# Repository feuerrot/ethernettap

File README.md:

# Ethernettap

Passive ethernet tap, build after [this](http://itgeekchronicles.co.uk/2011/09/21/random-diy-passive-ethernet-tap-or-pet/) instruction.

I've never tested the layout, so you maybe want to do that first, because I'm not responsible for whatever you do with this hardware.

The RJ45-connector is from [Pollin](http://www.pollin.de) and it's called [Western-Modularbuchse FCI 748729-3011](http://www.pollin.de/shop/dt/OTk5ODQ1OTk-/Bauelemente_Bauteile/Mechanische_Bauelemente/Steckverbinder_Klemmen/Western_Modularbuchse_FCI_748729_3011.html) and 4 of them costs 1,20€ so maybe the whole tap costs something below 5€.

## Layout

### Top

### Bottom

### Combined

### Combined as gif

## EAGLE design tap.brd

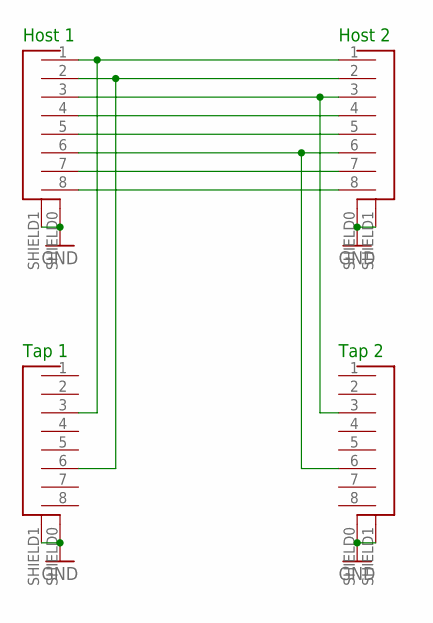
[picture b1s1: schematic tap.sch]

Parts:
HOST1, HOST2: 451000; RJ45
TAP1, TAP2: 451000; RJ45

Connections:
GND: HOST1.SHIELD0, HOST1.SHIELD1, HOST2.SHIELD0, HOST2.SHIELD1, TAP1.SHIELD0, TAP1.SHIELD1, TAP2.SHIELD0, TAP2.SHIELD1
unnamed: HOST1.1, HOST2.1, TAP1.3
unnamed: HOST1.2, HOST2.2, TAP1.6
unnamed: HOST1.3, HOST2.3, TAP2.3
unnamed: HOST1.4, HOST2.4
unnamed: HOST1.5, HOST2.5
unnamed: HOST1.6, HOST2.6, TAP2.6
unnamed: HOST1.7, HOST2.7
unnamed: HOST1.8, HOST2.8

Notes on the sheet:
Host 1
Host 2
Tap 1
Tap 2

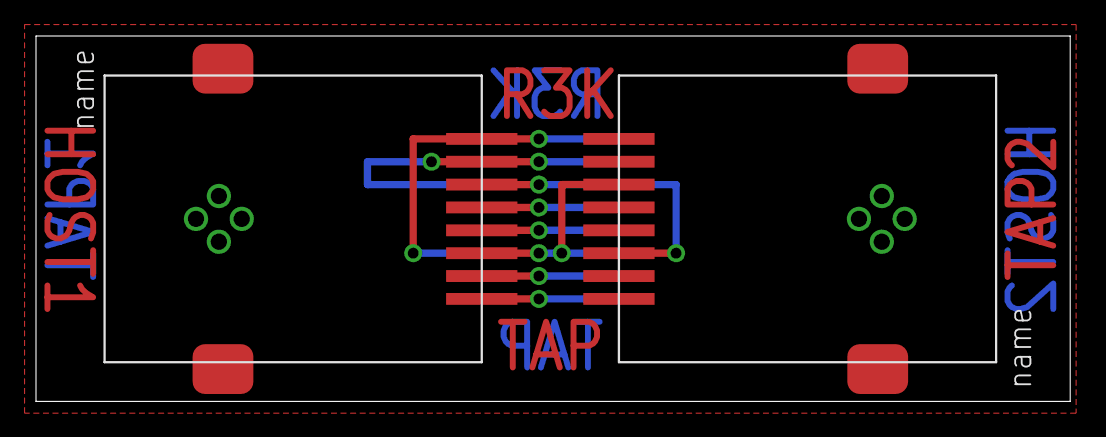
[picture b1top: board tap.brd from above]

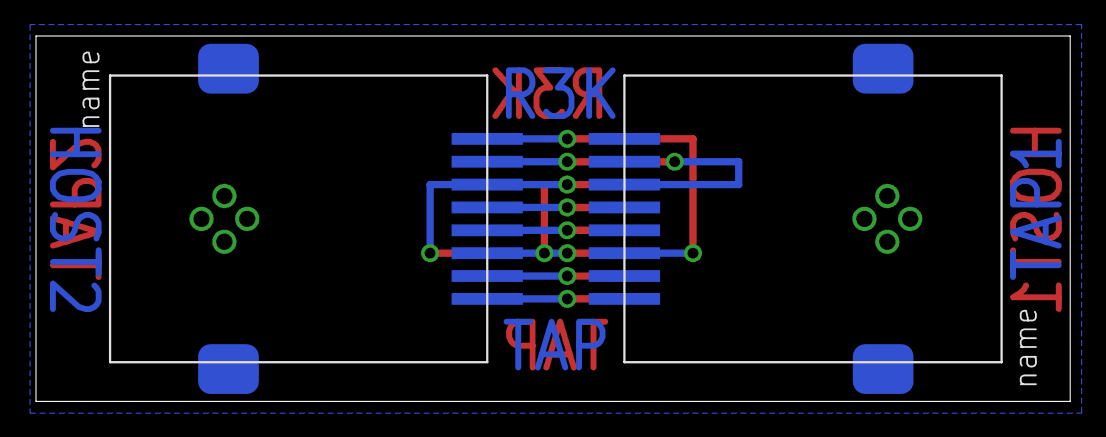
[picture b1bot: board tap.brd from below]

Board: 2 copper layers, 57.5 x 20.3 mm, 4 parts (2 on the bottom side), 9 nets.

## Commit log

2013-05-30 Images for the circuit and the boards
2013-05-30 Adding images to the readme
2013-05-30 fixing the readme
2013-05-30 I should learn how to markdown
    Or I should use some sort of preview…
2013-05-30 Fixing some minor pseudobug and rotating the whole board
2013-05-30 Fixing some minor bug, again
    Moving the Host1 and Tap2 labels
2013-05-30 Still doing things with the readme
    Setext-style headers => Atx-style headers
2013-05-31 Moving some other texts
    This should be the final version
2013-05-31 Fuck yeah, gif!
2013-05-31 Subdir for the images
    Will it break the markdown?
2013-05-31 Adding eagle project file
    Eagle wants this file to recognise it as a project
2013-06-07 removing TMI
